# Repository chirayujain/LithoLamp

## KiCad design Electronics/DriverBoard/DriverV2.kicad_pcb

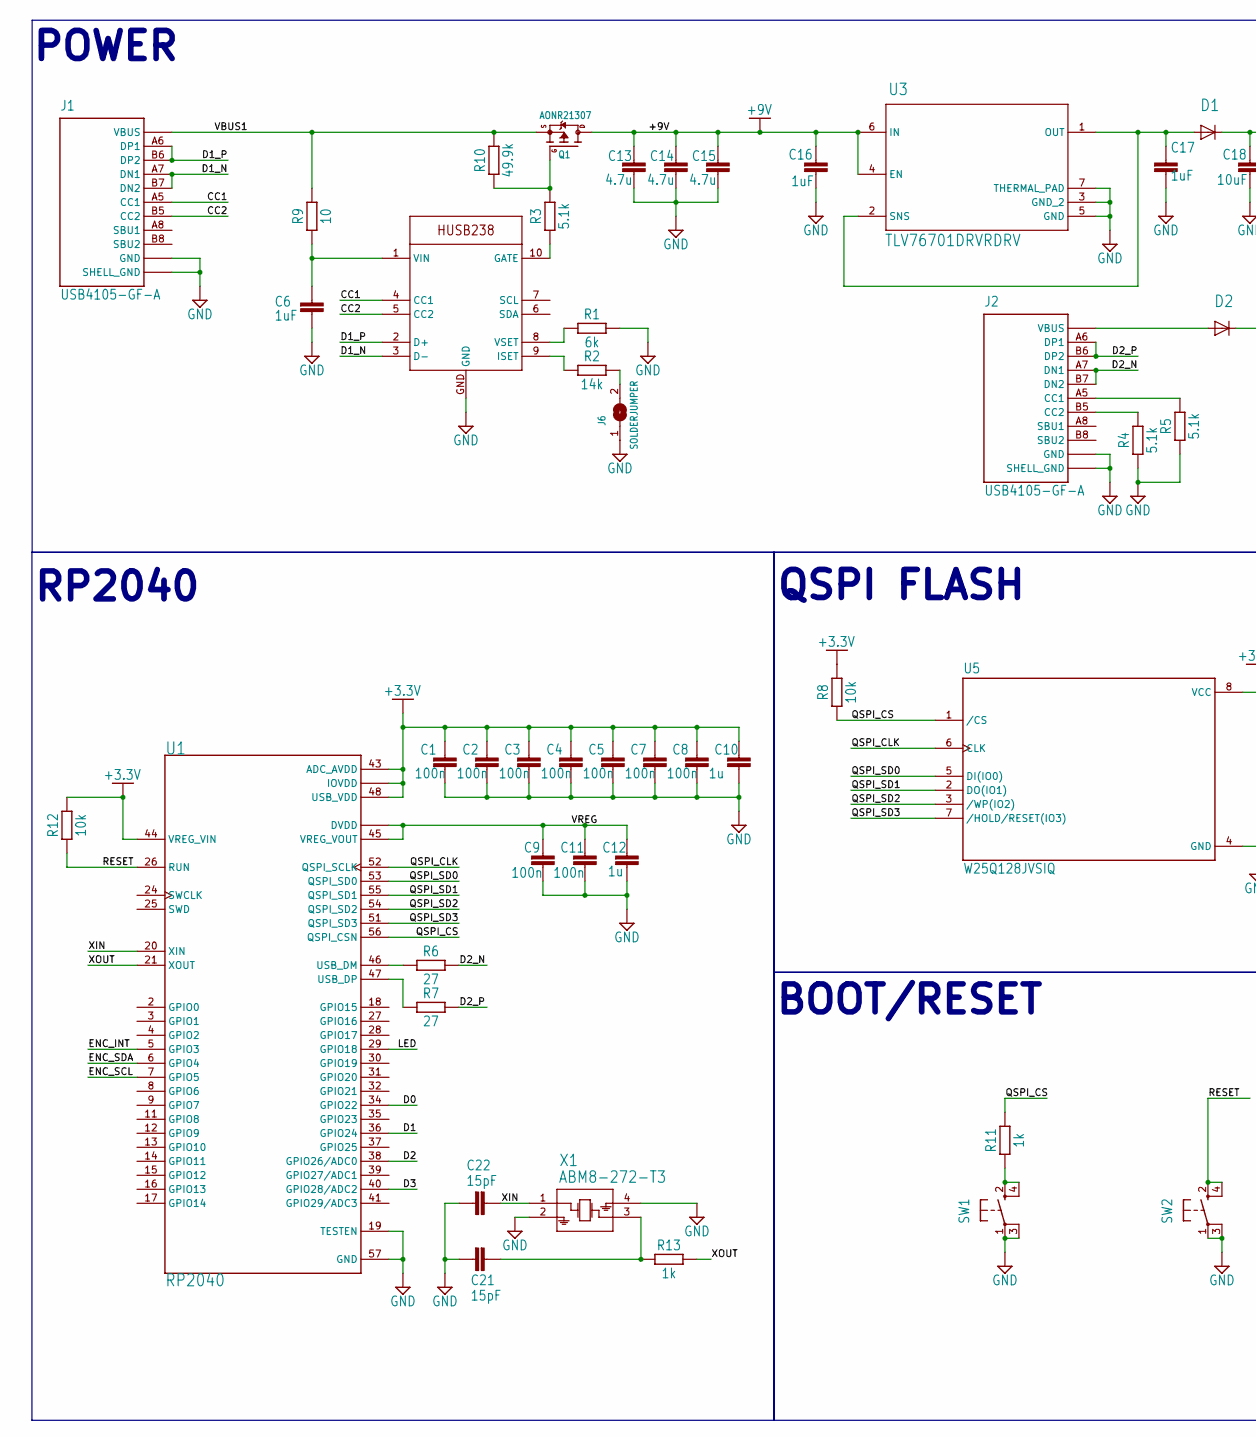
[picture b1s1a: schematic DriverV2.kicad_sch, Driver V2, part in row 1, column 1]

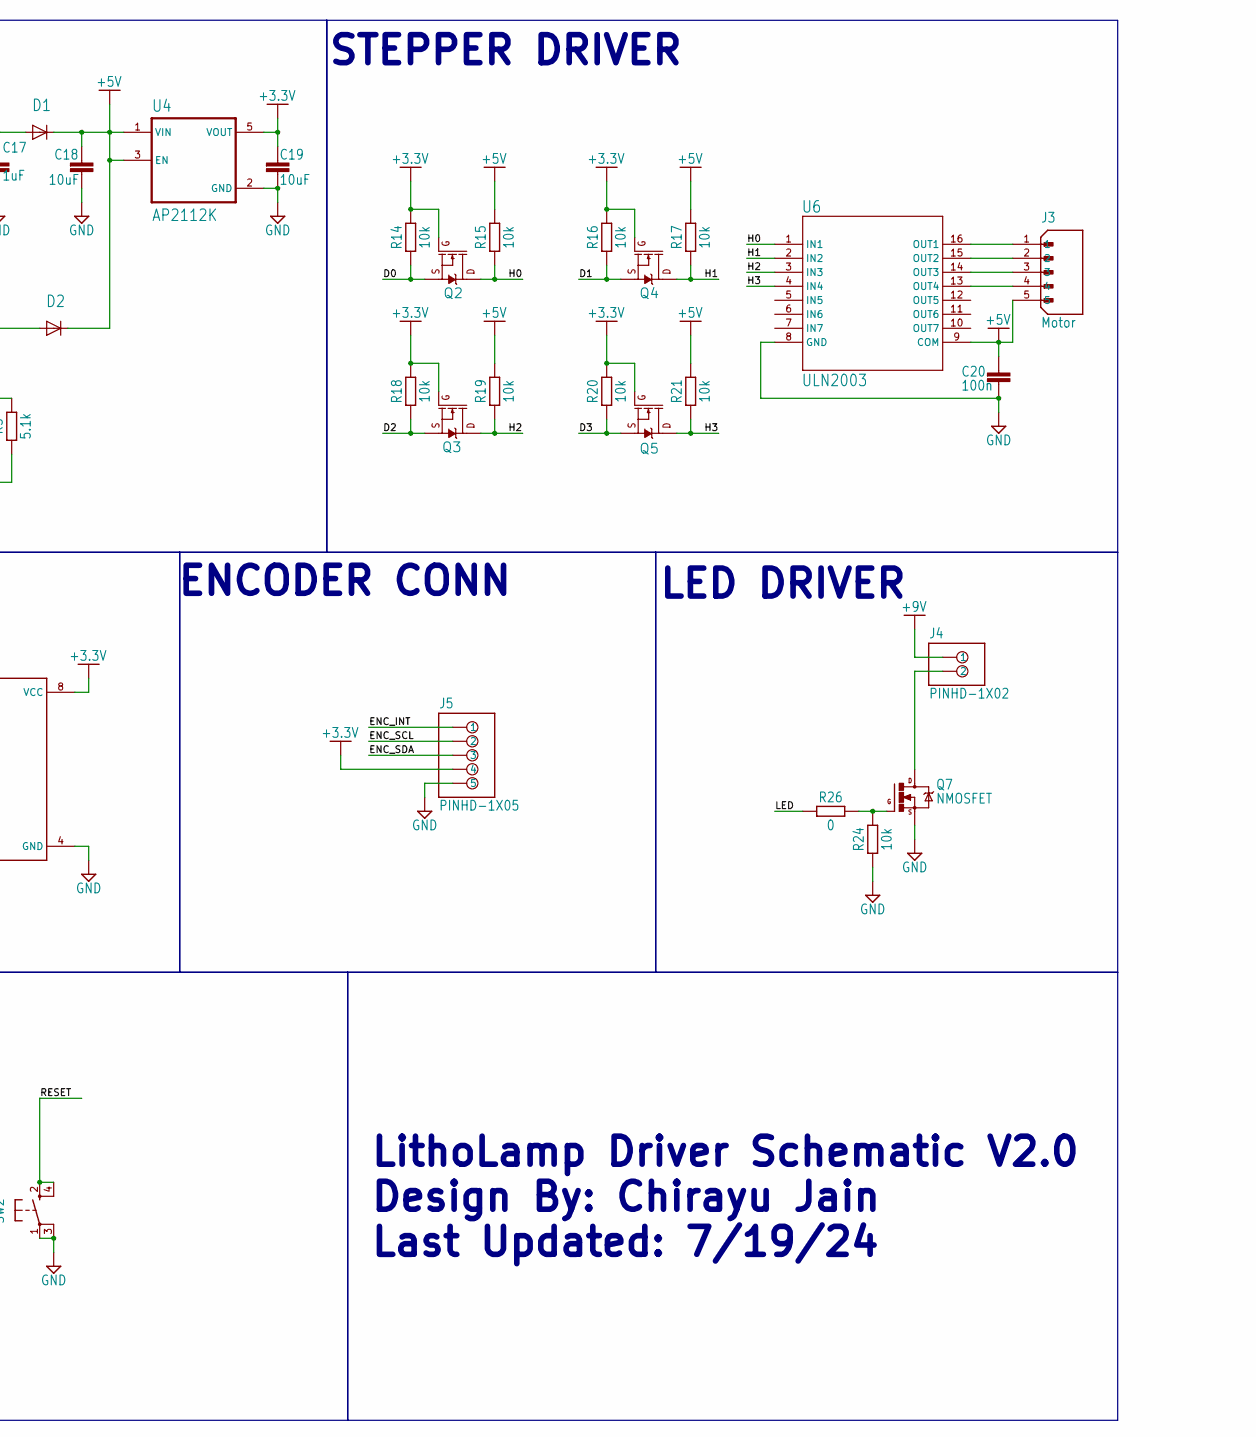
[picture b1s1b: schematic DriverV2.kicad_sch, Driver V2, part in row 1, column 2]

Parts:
C1, C2, C3, C4, C5, C7, C8, C9, C11: 100n; CAPC1005X60
C6, C16, C17: 1uF; CAPC1608X85
C10, C12: 1u; CAPC1005X60
C13, C14, C15: 4.7u; CAPC1608X85
C18, C19: 10uF; CAPC1608X85
C20: 100n; CAPC1608X85
C21, C22: 15pF; CAPC1608X85
D1, D2: NSR0320MW2T1GSOD-323_1P8X1P35_ONS-M; SOD-323_1P8X1P35_ONS-M
J1, J2: USB4105-GF-A; GCT_USB4105-GF-A
J3: Motor; JST_B5B-XH-A(LF)(SN)
J4: PINHD-1X02; 1X02
J5: PINHD-1X05; 1X05
J6: SOLDERJUMPER; SOLDERJUMPER_ARROW_NOPASTE
Q1: AONR21307; POWERDI3333
Q2, Q3, Q4, Q5: 220mA/50V/3.5Ω; SOT23-3
Q7: NMOSFET; SOT23
R1: 6k; RESC1608X60
R2: 14k; RESC1608X60
R3, R4, R5: 5.1k; RESC1608X60
R6, R7: 27; RESC1608X60
R8, R12, R14, R15, R16, R17, R18, R19, R20, R21, R24: 10k; RESC1608X60
R9: 10; RESC1608X60
R10: 49.9k; RESC1608X60
R11, R13: 1k; RESC1608X60
R26: 0; RESC1608X60
SW1, SW2: RESET; KMR2
U1: RP2040; QFN40P700X700X90-57N
U2: HUSB238; DFN10_3X3MM
U3: TLV76701DRVRDRV; DRV0006A-IPC_A
U4: AP2112K; SOT95P285X140-5N
U5: W25Q128JVSIQ; SOIC127P790X216-8N
U6: ULN2003; SO-16_STM-M
X1: ABM8-272-T3; ABM8-272-T3_ABR

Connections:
+3.3V: C1.1, C2.1, C3.1, C4.1, C5.1, C7.1, C8.1, C10.1, C19.1, J5.4, Q2.1 (G), Q3.1 (G), Q4.1 (G), Q5.1 (G), R8.2, R12.2, R14.2, R16.2, R18.2, R20.2, U1.1 (IOVDD), U1.10 (IOVDD), U1.22 (IOVDD), U1.33 (IOVDD), U1.42 (IOVDD), U1.43 (ADC_AVDD), U1.44 (VREG_VIN), U1.48 (USB_VDD), U1.49 (IOVDD), U4.5 (VOUT), U5.8 (VCC)
+5V: C18.1, C20.1, D1.1 (CATHODE), D2.1 (CATHODE), J3.5, R15.2, R17.2, R19.2, R21.2, U4.1 (VIN), U4.3 (EN), U6.9 (COM)
+9V: C13.1, C14.1, C15.1, C16.1, J4.1, Q1.5678 (D), U3.4 (EN), U3.6 (IN)
CC1: J1.A5 (CC1), U2.4 (CC1)
CC2: J1.B5 (CC2), U2.5 (CC2)
D0: Q2.2 (S), R14.1, U1.34 (GPIO22)
D1: Q4.2 (S), R16.1, U1.36 (GPIO24)
D1_N: J1.A7 (DN1), J1.B7 (DN2), U2.3 (D-)
D1_P: J1.A6 (DP1), J1.B6 (DP2), U2.2 (D+)
D2: Q3.2 (S), R18.1, U1.38 (GPIO26/ADC0)
D2_N: J2.A7 (DN1), J2.B7 (DN2), R6.2
D2_P: J2.A6 (DP1), J2.B6 (DP2), R7.2
D3: Q5.2 (S), R20.1, U1.40 (GPIO28/ADC2)
D+: R7.1, U1.47 (USB_DP)
D-: R6.1, U1.46 (USB_DM)
ENC_INT: J5.1, U1.5 (GPIO3)
ENC_SCL: J5.2, U1.7 (GPIO5)
ENC_SDA: J5.3, U1.6 (GPIO4)
GATE: R3.1, U2.10 (GATE)
H0: Q2.3 (D), R15.1, U6.1 (IN1)
H1: Q4.3 (D), R17.1, U6.2 (IN2)
H2: Q3.3 (D), R19.1, U6.3 (IN3)
H3: Q5.3 (D), R21.1, U6.4 (IN4)
ISET: R2.1, U2.9 (ISET)
LED: R26.1, U1.29 (GPIO18)
unnamed: C6.1, R9.1, U2.1 (VIN)
unnamed: Q1.4 (G), R3.2, R10.1
unnamed: J6.2, R2.2
unnamed: J2.A5 (CC1), R5.2
unnamed: J2.B5 (CC2), R4.2
unnamed: D2.2 (ANODE), J2.A4_B9 (VBUS), J2.B4_A9 (VBUS)
unnamed: C17.1, D1.2 (ANODE), U3.1 (OUT), U3.2 (SNS)
unnamed: J3.1, U6.16 (OUT1)
unnamed: R11.1, SW1.2 (S), SW1.4 (S1)
unnamed: C21.1, R13.1, X1.3
unnamed: J3.2, U6.15 (OUT2)
unnamed: J3.3, U6.14 (OUT3)
unnamed: J3.4, U6.13 (OUT4)
unnamed: J4.2, Q7.3 (D)
unnamed: Q7.1 (G), R24.2, R26.2
QSPI_CLK: U1.52 (QSPI_SCLK), U5.6 (CLK)
QSPI_CS: R8.1, R11.2, U1.56 (QSPI_CSN), U5.1 (/CS)
QSPI_SD0: U1.53 (QSPI_SD0), U5.5 (DI(IO0))
QSPI_SD1: U1.55 (QSPI_SD1), U5.2 (DO(IO1))
QSPI_SD2: U1.54 (QSPI_SD2), U5.3 (/WP(IO2))
QSPI_SD3: U1.51 (QSPI_SD3), U5.7 (/HOLD/RESET(IO3))
RESET: R12.1, SW2.2 (S), SW2.4 (S1), U1.26 (RUN)
VBUS1: J1.A4_B9 (VBUS), J1.B4_A9 (VBUS), Q1.1 (S), Q1.2 (S), Q1.3 (S), R9.2, R10.2
VREG: C9.1, C11.1, C12.1, U1.23 (DVDD), U1.45 (VREG_VOUT), U1.50 (DVDD)
VSET: R1.1, U2.8 (VSET)
XIN: C22.1, U1.20 (XIN), X1.1
XOUT: R13.2, U1.21 (XOUT)

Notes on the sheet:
LithoLamp Driver Schematic V2.0 Design By: Chirayu Jain Last Updated: 7/19/24
STEPPER DRIVER
RP2040
QSPI FLASH
ENCODER CONN
BOOT/RESET
LED DRIVER
POWER

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
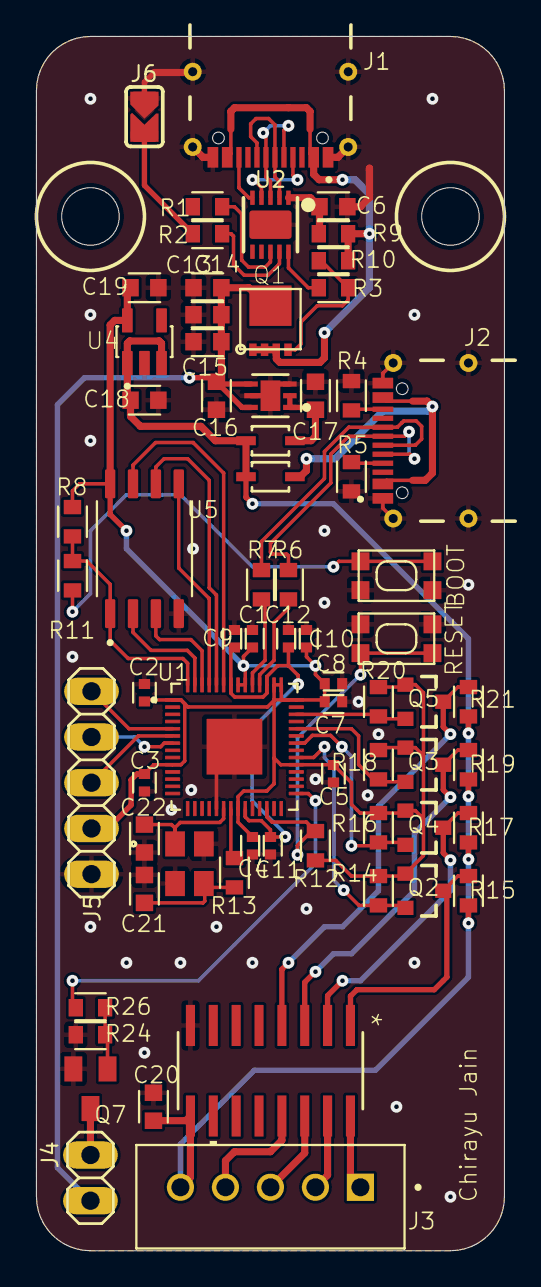
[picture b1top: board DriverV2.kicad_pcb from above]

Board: 2 copper layers, 26.0 x 67.5 mm, 70 parts (0 on the bottom side), 53 nets.

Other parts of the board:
@HOLE0, @HOLE1: (no value)

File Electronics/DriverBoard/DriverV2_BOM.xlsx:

Item # | REFDES | Qty | Manufacturer | MPN/Link | Value/Description | Package
1 | R1 | 1 | YAGEO | RC0603FR-076K04L | 6k | R_0603
2 | R2 | 1 | YAGEO | RC0603FR-0714KL | 14k | R_0603
3 | R3, R4, R5 | 3 | YAGEO | RC0603FR-075K1L | 5.1k | R_0603
4 | R6, R7 | 2 | YAGEO | RC0603JR-0727RL | 27 | R_0603
5 | R8, R12, R14, R15, R16, R17, R18, R19, R20, R21, R24 | 11 | YAGEO | RC0603FR-0710KL | 10k | R_0603
6 | R9 | 1 | Stackpole Electronics | RMCF0603FT10R0 | 10 | R_0603
7 | R10 | 1 | YAGEO | RC0603FR-0749K9L | 49.9k | R_0603
8 | R11, R13 | 2 | YAGEO | RC0603FR-071KL | 1k | R_0603
9 | R26 | 1 |  |  | 0 | R_0603
10 | C1, C2, C3, C4, C5, C7, C8, C9, C11 | 9 | Murata | GRM155R71C104KA88J | 100n | C_0402
11 | C6, C16, C17 | 3 | YAGEO | CC0603KRX7R7BB105 | 1uF | C_0603
12 | C10, C12 | 2 | Taiyo Yuden | LMK105BJ105KV-F | 1u | C_0402
13 | C13, C14, C15 | 3 | Murata | GRT188R61E475KE13D | 4.7uF | C_0603
14 | C18, C19 | 2 | Murata | GRM188R61E106MA73D | 10uF | C_0603
15 | C20 | 1 | Murata | GCM188R71H104KA57J | 100n | C_0603
16 | C21, C22 | 2 | Walsin Technology | 0603N150F500CT | 15pF | C_0603
17 | D1, D2 | 2 | Onsemi | NSR0320MW2T1G | NSR0320MW2T1G | SOD-323
18 | Q1 | 1 | Alpha & Omega Semiconductor | AONR21307 | AONR21307 | 8-DFN-EP (3x3)
19 | Q2, Q3, Q4, Q5 | 4 | Onsemi | BSS138 | BSS138 | SOT23-3
20 | Q7 | 1 | Alpha & Omega Semiconductor | AO3422 | AO3422 | SOT23-3
21 | X1 | 1 | Abracon | ABM8-272-T3 | 12MHz Crystal | 4-SMD
22 | U1 | 1 | Raspberry Pi | SC0914(13) | RP2040 | QFN40P700X700X90-57N
23 | U2 | 1 |  |  | HUSB238 | DFN10_3X3MM
24 | U3 | 1 | Texas Instruments | TLV76750DRVR | TLV76701DRVR | 6-WSON (2x2)
25 | U4 | 1 | Diodes Inc. | AP2112K-3.3TRG1 | AP2112K-3.3TRG1 | SOT-25
26 | U5 | 1 | Winbond Electronics | W25Q128JVSIQ TR | W25Q128JVSIQ | SOIC127P790X216-8N
27 | U6 | 1 | STMicroelectronics | ULN2003D1013TR | ULN2003D | SO-16_STM-M
28 | SW1, SW2 | 2 | C&K | KMR211NG LFS | SPST_TACT-KMR2 | KMR2
29 | J1, J2 | 2 | GCT | USB4105-GF-A | USB4105-GF-A | GCT_USB4105-GF-A
30 | J3 | 1 | JST | B5B-XH-A | B5B-XH | JST_B5B-XH-A(LF)(SN)
31 | J4 | 1 |  |  | PINHD-1X02_1X02M | 1X02
32 | J5 | 1 |  |  | PINHD-1X05_1X05M | 1X05
33 | J6 | 1 |  |  | Solder Jumper | SOLDERJUMPER_ARROW_NOPASTE

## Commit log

2025-01-18 Source Upload
2025-01-18 Create LICENSE
